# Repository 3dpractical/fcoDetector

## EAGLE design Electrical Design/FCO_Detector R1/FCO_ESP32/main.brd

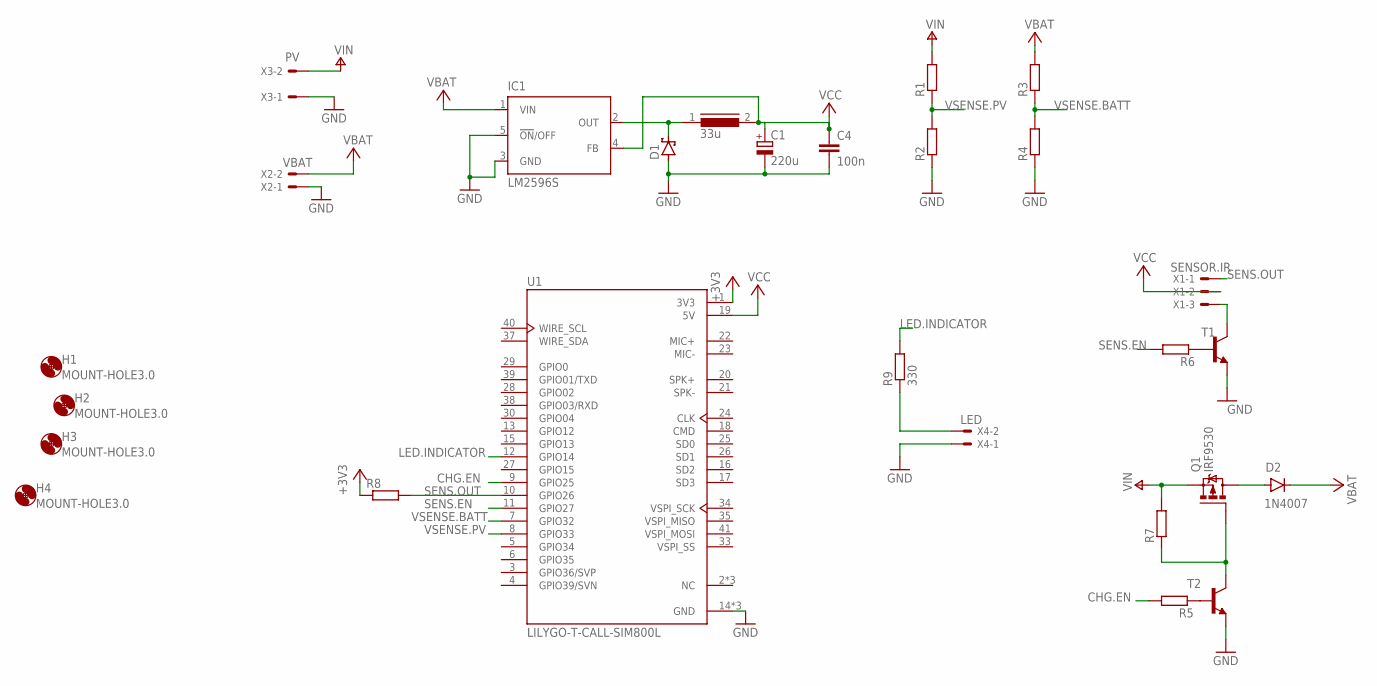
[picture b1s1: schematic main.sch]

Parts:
C1: 220u; 153CLV-0810
C4: 100n; C0805
D1: SCHOTTKY-DIODESMD; SMB
D2: 1N4007; DO-41
H1, H2, H3, H4: MOUNT-HOLE3.0; 3,0
IC1: LM2596S; TO263-5
L2: 33u; DR125
Q1: IRF9530; TO220BV
R1, R2, R3, R4, R8: R-EU_R0805; R0805
R5, R6, R7: R-EU_0207/7; 0207/7
R9: 330; R0805
T1, T2: -NPN-TO92-ECB; TO92-ECB
U1: LILYGO-T-CALL-SIM800L; XCVR_LILYGO-T-CALL-SIM800L
X1: SENSOR.IR; JST-XH-03-PACKAGE-LONG-PAD
X2: VBAT; JST-XH-02-PACKAGE-LONG-PAD
X3: PV; KK-156-2
X4: LED; JST-XH-02-PACKAGE-LONG-PAD

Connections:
+3V3: R8.1, U1.1 (3V3)
+5V: D2.C, IC1.1 (VIN), R3.2, X2.2
CHG.EN: R5.2, U1.9 (GPIO25)
GND: C1.-, C4.2, D1.A, IC1.3 (GND), IC1.5 (!ON!/OFF), R2.1, R4.1, T1.E, T2.E, U1.14 (GND), U1.36 (GND), U1.42 (GND), X2.1, X3.1, X4.1
LED.INDICATOR: R9.2, U1.12 (GPIO14)
MIC+: U1.22 (MIC+)
MIC-: U1.23 (MIC-)
unnamed: T1.C, X1.3
unnamed: R6.1, T1.B
unnamed: R9.1, X4.2
unnamed: D1.C, IC1.2 (OUT), L2.1
unnamed: Q1.G, R7.1, T2.C
unnamed: D2.A, Q1.D
unnamed: R5.1, T2.B
NC: U1.2 (NC), U1.31 (NC), U1.32 (NC)
SENS.EN: R6.2, U1.11 (GPIO27)
SENS.OUT: R8.2, U1.10 (GPIO26), X1.1
SPK+: U1.20 (SPK+)
SPK-: U1.21 (SPK-)
V+: Q1.S, R1.2, R7.2, X3.2
VCC: C1.+, C4.1, IC1.4 (FB), L2.2, U1.19 (5V), X1.2
VSENSE.BATT: R3.1, R4.2, U1.7 (GPIO32)
VSENSE.PV: R1.1, R2.2, U1.8 (GPIO33)

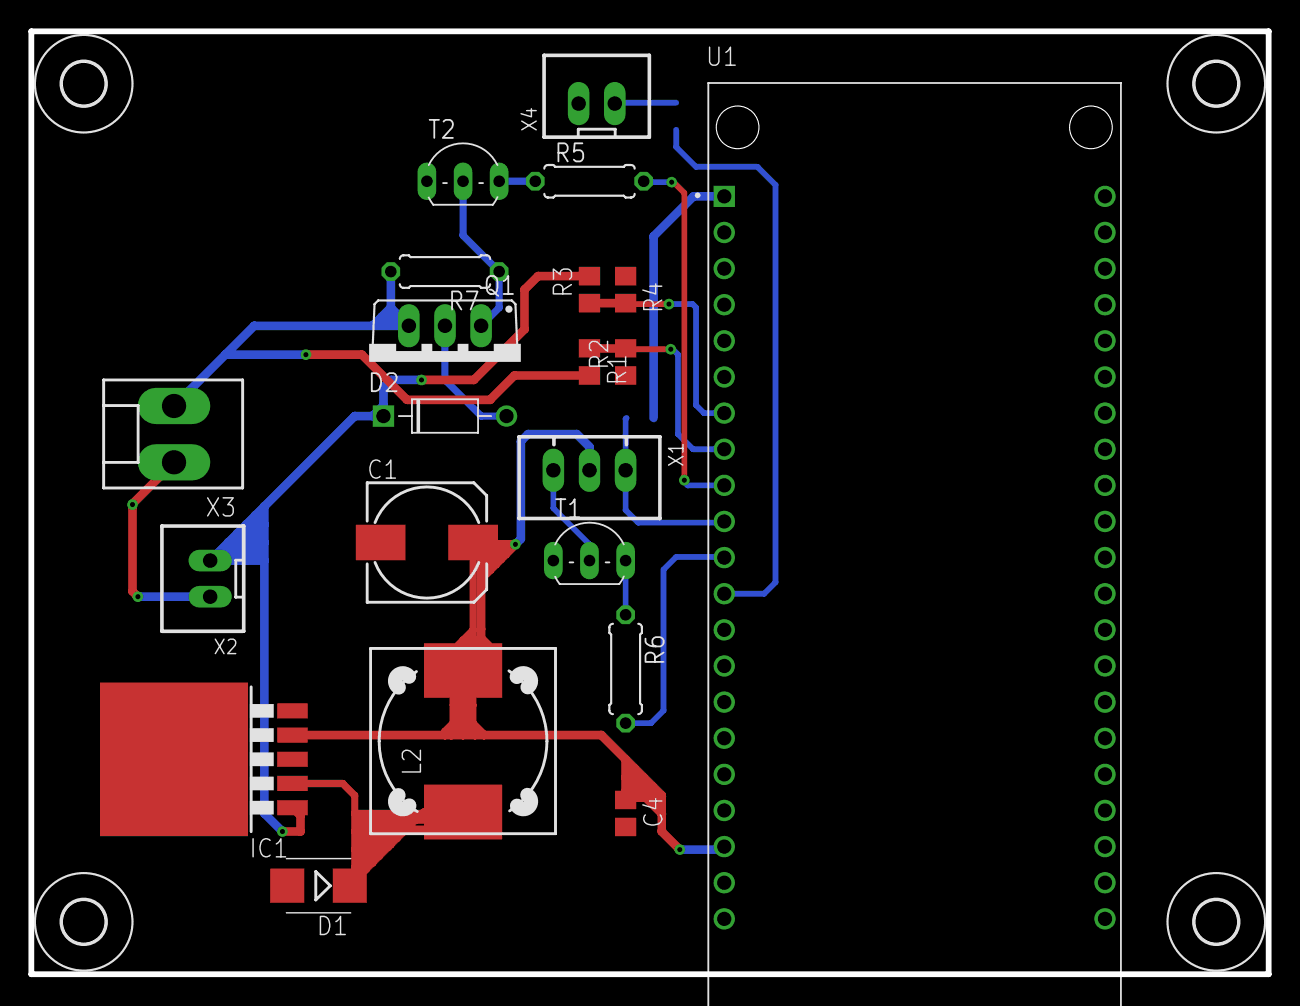
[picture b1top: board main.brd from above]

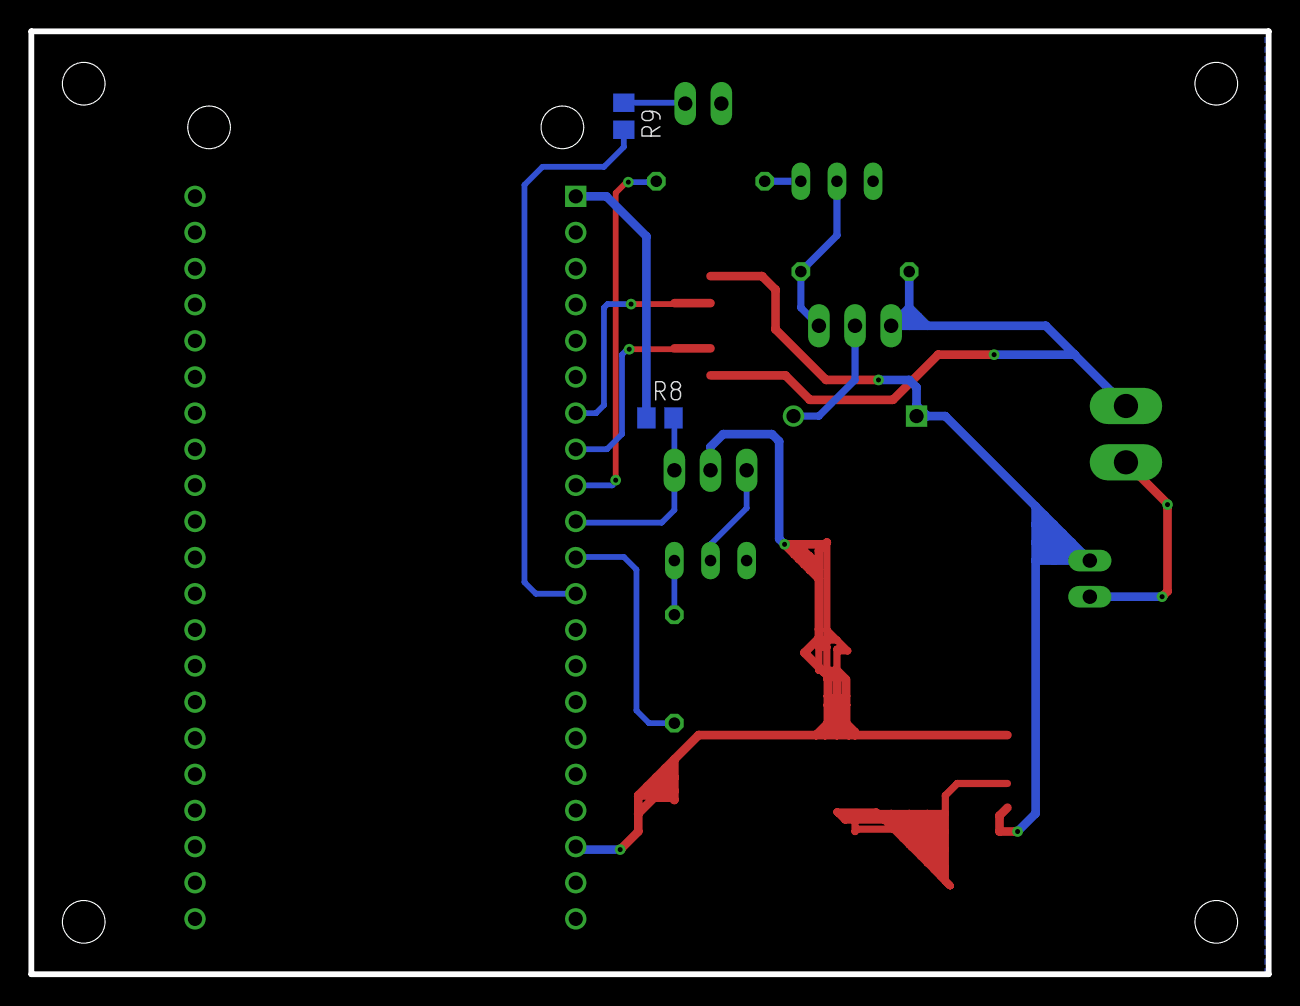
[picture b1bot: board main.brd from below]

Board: 2 copper layers, 87.0 x 66.3 mm, 27 parts (2 on the bottom side), 19 nets.
